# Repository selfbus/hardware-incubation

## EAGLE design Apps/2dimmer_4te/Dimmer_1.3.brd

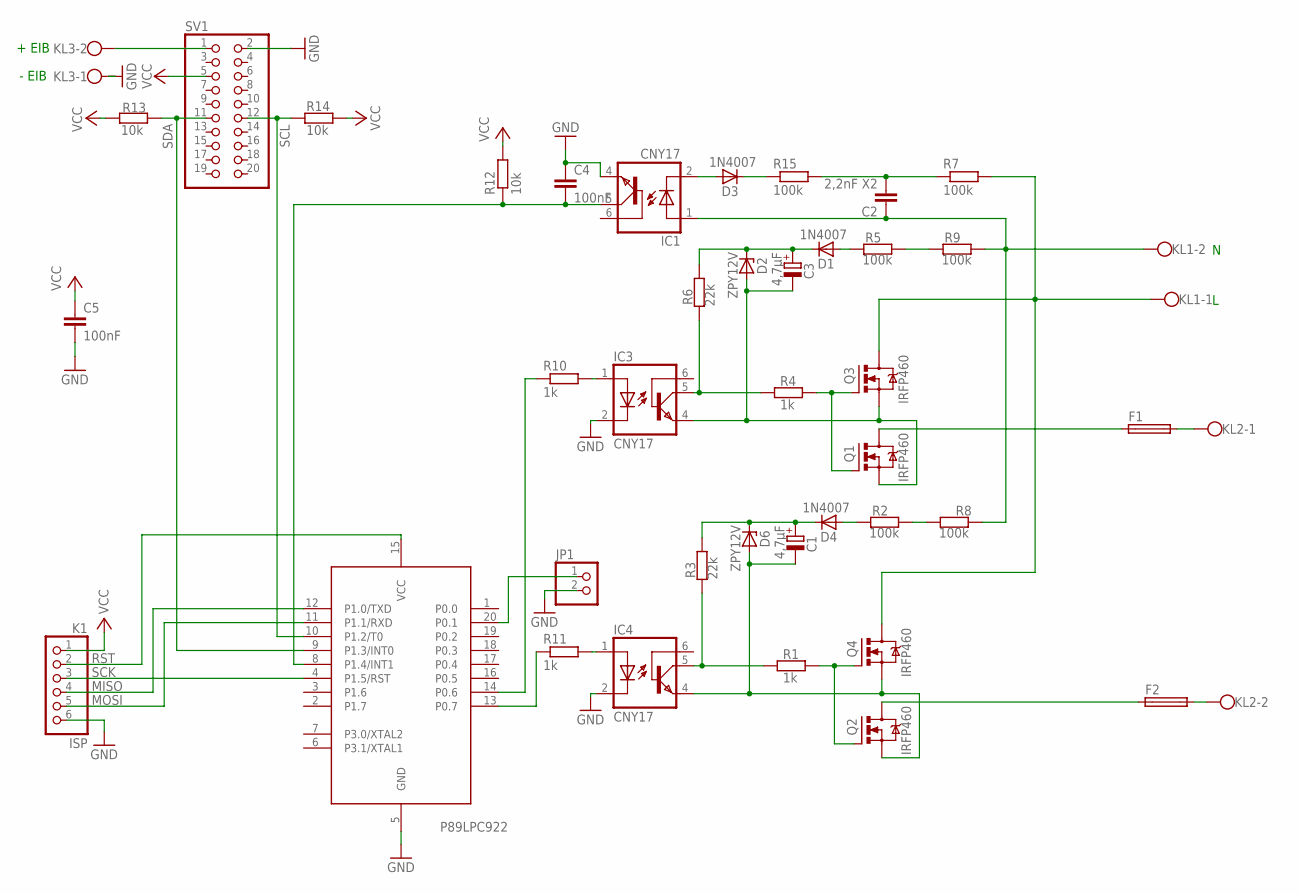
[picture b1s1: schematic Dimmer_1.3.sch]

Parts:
C1, C3: 4,7µF; E2-4
C2: 2,2nF X2; C075-063X106
C4: 100nF; C050-024X044
C5: 100nF; C025-024X044
D1, D3, D4: 1N4007; DO35-10
D2, D6: ZPY12V; DO41Z10
F1, F2: SH22,5
IC1, IC3, IC4: CNY17; DIL06
IC2: 89LPC922; DIL20
JP1: PINHD-1X2; 1X02
K1: ISP; 1X06
KL1, KL2, KL3: W237-102
Q1, Q2, Q3, Q4: IRFP460; TO247BV
R1, R4, R10, R11: 1k; 0204/7
R2, R5, R7, R8, R9, R15: 100k; 0204/7
R3, R6: 22k; 0204/7
R12, R13, R14: 10k; 0204/7
SV1: PINHD-2X10; 2X10

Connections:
GND: C4.1, C5.2, IC1.4 (EMI), IC2.5 (GND), IC3.2 (C), IC4.2 (C), JP1.2, K1.6, KL3.1, SV1.2
MISO: IC2.12 (P1.0/TXD), K1.4
MOSI: IC2.11 (P1.1/RXD), K1.5
unnamed: C4.2, IC1.5 (COL), IC2.8 (P1.4/INT1), R12.1
unnamed: D3.A, IC1.2 (C)
unnamed: C2.1, IC1.1 (A), KL1.2, R8.2, R9.2
unnamed: IC3.1 (A), R10.2
unnamed: IC2.14 (P0.6), R10.1
unnamed: Q1.G, Q3.G, R4.2
unnamed: IC2.13 (P0.7), R11.1
unnamed: KL1.1, Q3.D, Q4.D, R7.2
unnamed: R5.2, R9.1
unnamed: D3.C, R15.1
unnamed: C1.+, D4.C, D6.C, R3.2
unnamed: C3.+, D1.C, D2.C, R6.2
unnamed: IC4.1 (A), R11.2
unnamed: F2.1, Q2.D
unnamed: D4.A, R2.1
unnamed: F1.2, KL2.1
unnamed: F2.2, KL2.2
unnamed: KL3.2, SV1.1
unnamed: C1.-, D6.A, IC4.4 (EMI), Q2.S, Q4.S
unnamed: IC4.5 (COL), R1.1, R3.1
unnamed: F1.1, Q1.D
unnamed: IC2.20 (P0.1), JP1.1
unnamed: C2.2, R7.1, R15.2
unnamed: D1.A, R5.1
unnamed: C3.-, D2.A, IC3.4 (EMI), Q1.S, Q3.S
unnamed: IC3.5 (COL), R4.1, R6.1
unnamed: R2.2, R8.1
unnamed: Q2.G, Q4.G, R1.2
RST: IC2.15 (VCC), K1.2
SCK: IC2.4 (P1.5/RST), K1.3
SCL: IC2.10 (P1.2/T0), R14.2, SV1.12
SDA: IC2.9 (P1.3/INT0), R13.1, SV1.11
VCC: C5.1, K1.1, R12.2, R13.2, R14.1, SV1.5

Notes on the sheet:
+ EIB
- EIB
P89LPC922

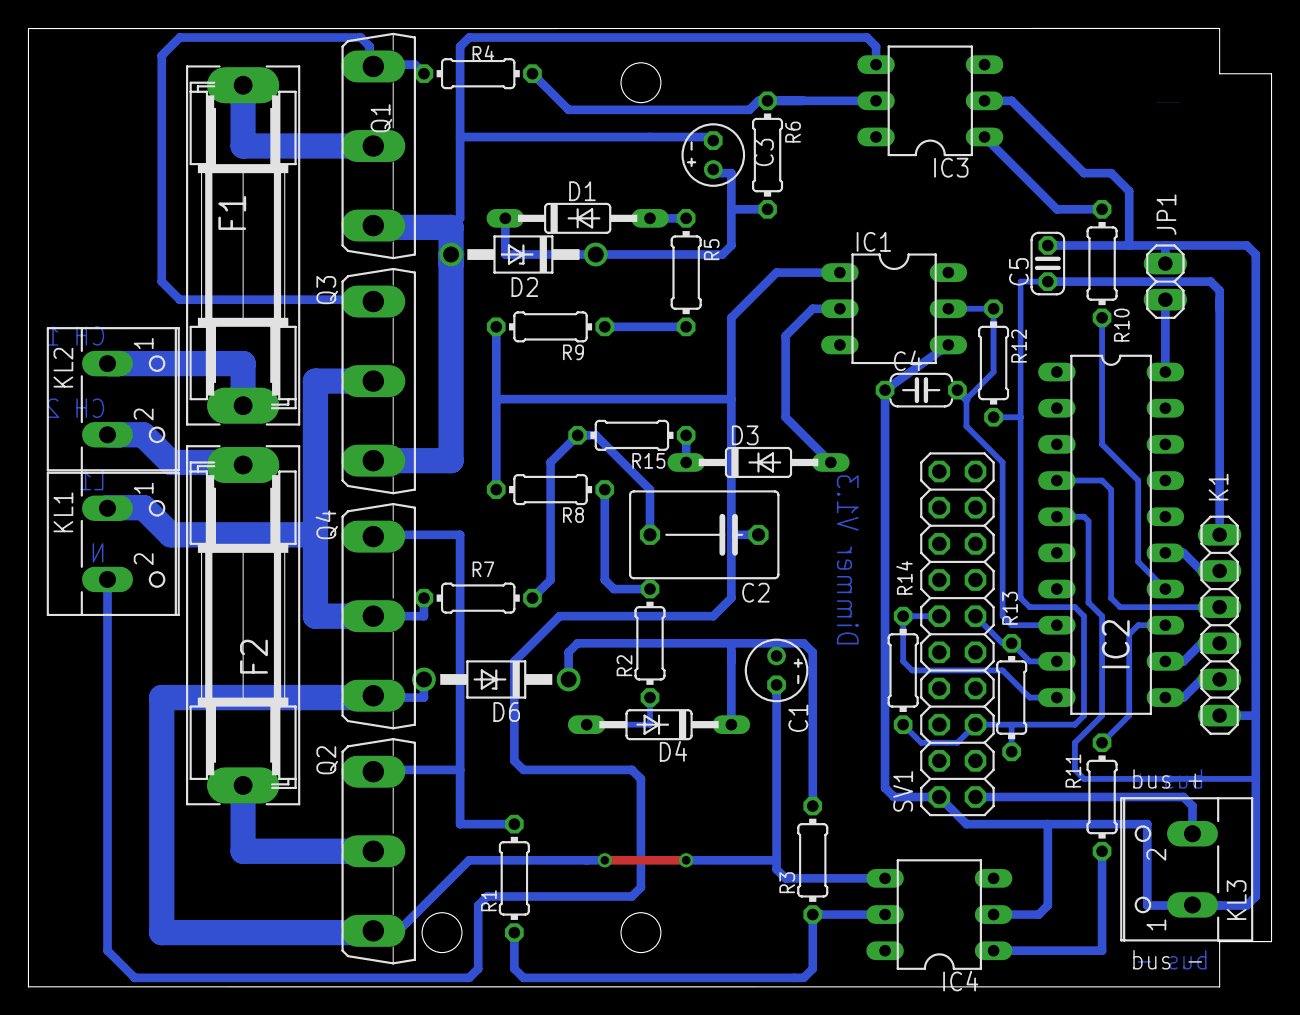
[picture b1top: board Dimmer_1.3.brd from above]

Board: 2 copper layers, 87.3 x 67.3 mm, 41 parts (0 on the bottom side), 36 nets.

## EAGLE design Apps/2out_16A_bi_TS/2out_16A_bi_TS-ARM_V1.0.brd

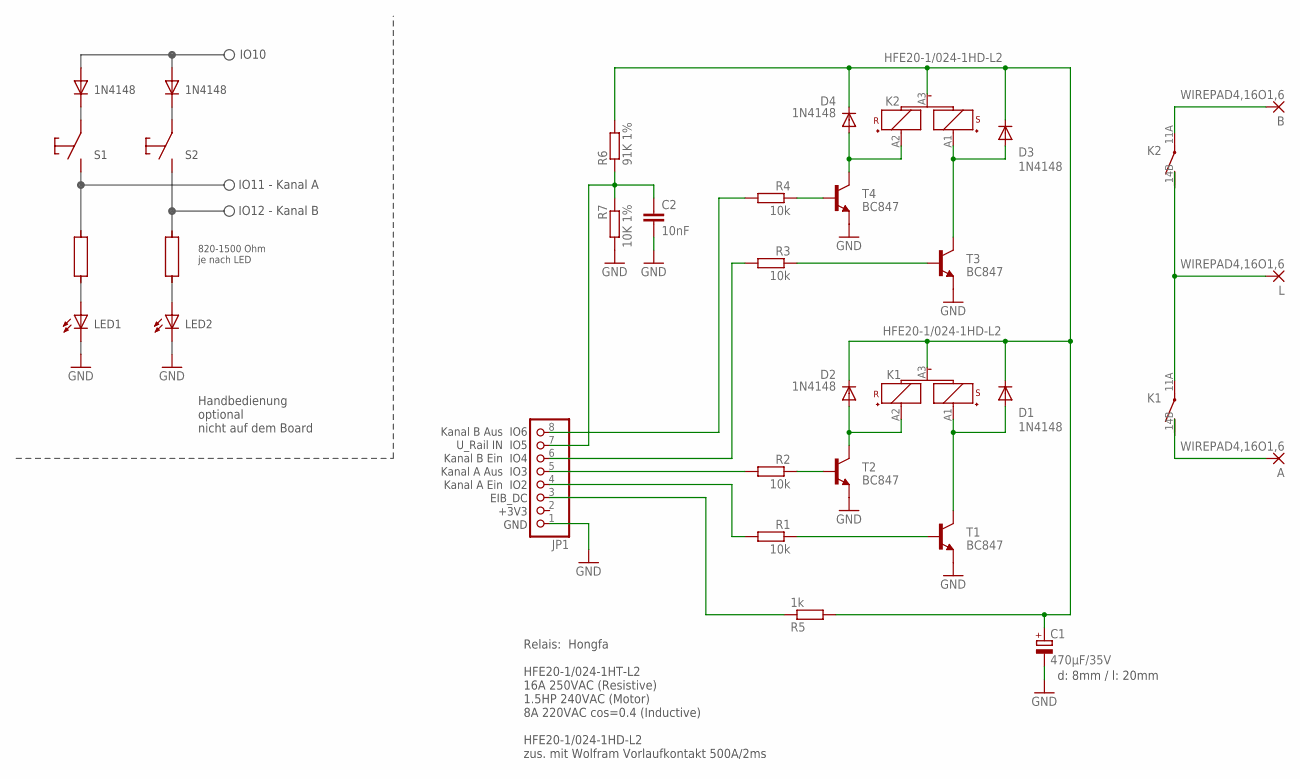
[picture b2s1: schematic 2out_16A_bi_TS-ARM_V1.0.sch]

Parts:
A: WIREPAD4,16O1,6; 4,16O1,6
B: WIREPAD4,16O1,6; 4,16O1,6
C1: 470µF/35V; E3,5-8
C2: 10nF; C1206K
D1, D2, D3, D4: 1N4148; MINIMELF
JP1: PINHD-1X8; 1X08
K1, K2: HFE20-1/024-1HD-L2; RT1-BI
L: WIREPAD4,16O1,6; 4,16O1,6
R1, R2, R3, R4: 10k; M1206
R5: 1k; M1206
R6: 91K 1%; M1206
R7: 10K 1%; M1206
T1, T2, T3, T4: BC847; SOT23
U$1, U$5: R_NUR_SCHALTPLAN; LEER
U$2, U$6: TASTE_NUR_SCHALTPLAN; LEER
U$3, U$7: LED_NUR_SCHALTPLAN; LEER
U$4, U$8: DIODE_NUR_SCHALTPLAN; LEER

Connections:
GND: C1.-, C2.2, JP1.1, R7.2, T1.2 (E), T2.2 (E), T3.2 (E), T4.2 (E)
unnamed: R1.1, T1.1 (B)
unnamed: JP1.5, R2.2
unnamed: A.1, K1.14B (SA)
unnamed: B.1, K2.11A (PA)
unnamed: K1.11A (PA), K2.14B (SA), L.1
unnamed: R2.1, T2.1 (B)
unnamed: JP1.6, R3.2
unnamed: C2.1, JP1.7, R6.1, R7.1
unnamed: D2.A, K1.A2 (R+), T2.3 (C)
unnamed: JP1.3, R5.1
unnamed: JP1.4, R1.2
unnamed: R3.1, T3.1 (B)
unnamed: R4.1, T4.1 (B)
unnamed: JP1.8, R4.2
R1: D1.A, K1.A1 (S+), T1.3 (C)
R2: D4.A, K2.A2 (R+), T4.3 (C)
R4: D3.A, K2.A1 (S+), T3.3 (C)
VDD_REL: C1.+, D1.C, D2.C, D3.C, D4.C, K1.A3 (-), K2.A3 (-), R5.2, R6.2

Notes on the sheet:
Kanal B Aus IO6 U_Rail IN IO5 Kanal B Ein IO4 Kanal A Aus IO3 Kanal A Ein IO2 EIB_DC +3V3 GND
Relais: Hongfa HFE20-1/024-1HT-L2 16A 250VAC (Resistive) 1.5HP 240VAC (Motor) 8A 220VAC cos=0.4 (Inductive) HFE20-1/024-1HD-L2 zus. mit Wolfram Vorlaufkontakt 500A/2ms
d: 8mm / l: 20mm
IO10
IO11 - Kanal A
IO12 - Kanal B
1N4148
820-1500 Ohm je nach LED
LED1
LED2
Handbedienung optional nicht auf dem Board

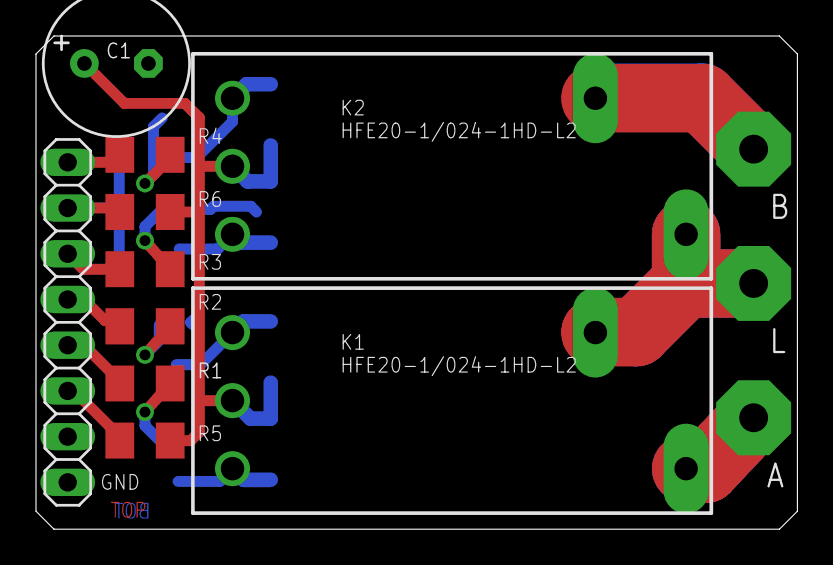
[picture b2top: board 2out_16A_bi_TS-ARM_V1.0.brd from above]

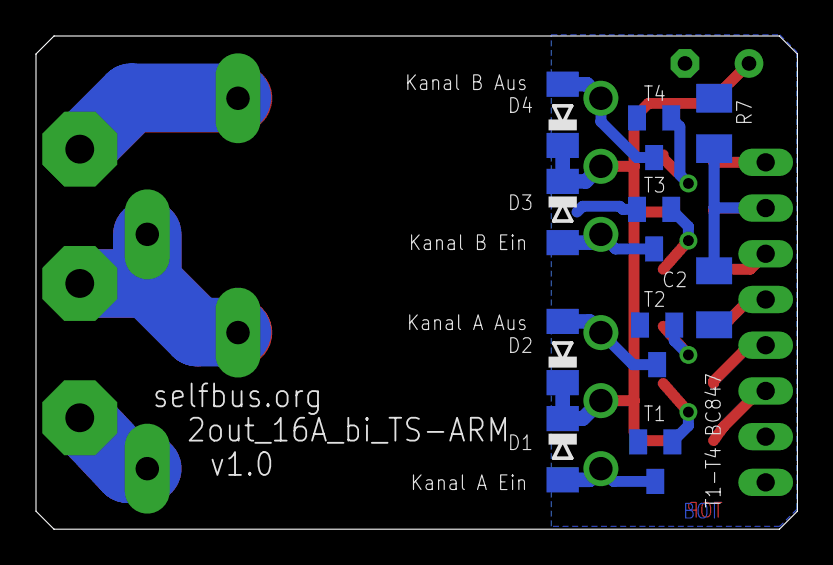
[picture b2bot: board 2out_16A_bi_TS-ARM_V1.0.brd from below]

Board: 2 copper layers, 42.3 x 27.4 mm, 31 parts (10 on the bottom side), 19 nets.
